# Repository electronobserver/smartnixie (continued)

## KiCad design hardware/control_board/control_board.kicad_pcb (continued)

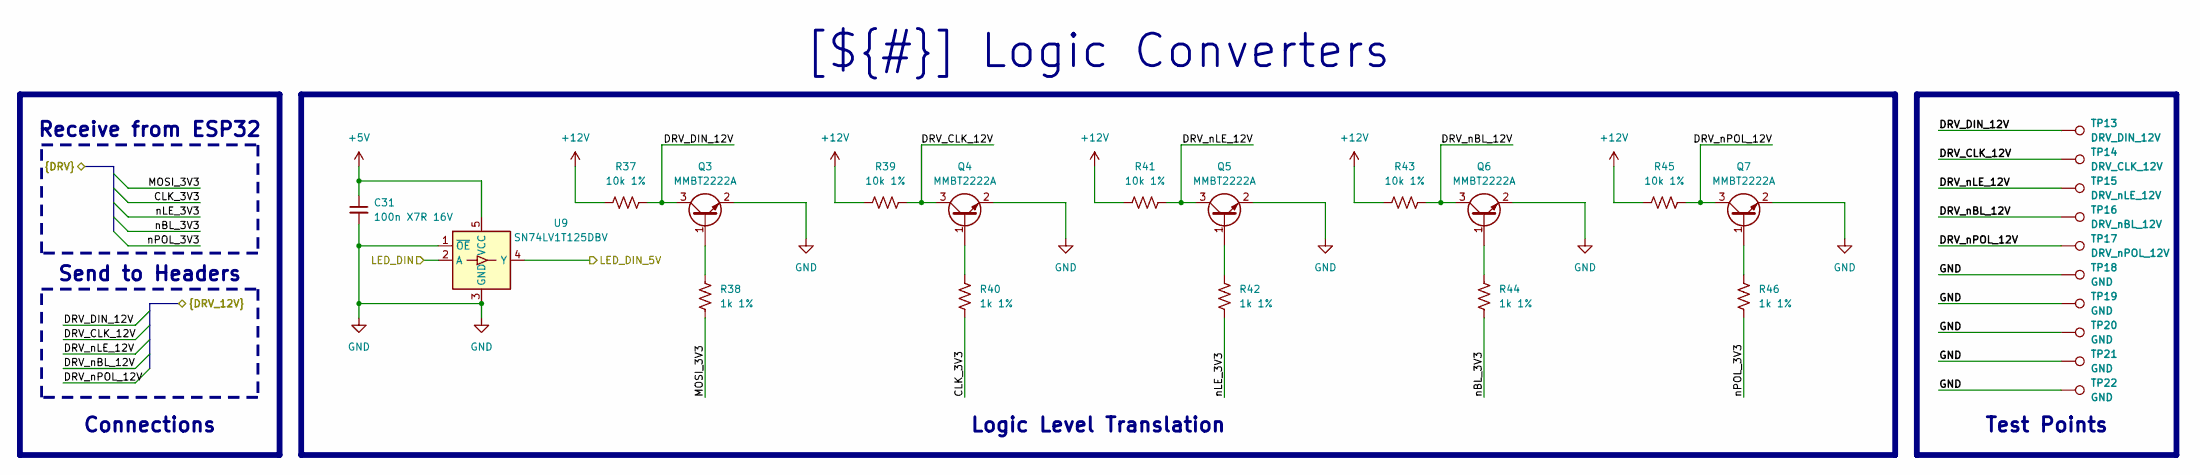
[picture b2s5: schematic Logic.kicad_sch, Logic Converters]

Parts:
C31: 100n X7R 16V; C_0805_2012Metric_Pad1.18x1.45mm_HandSolder; Part No. CC0805KRX7R7BB104
Q3, Q4, Q5, Q6, Q7: MMBT2222A; SOT-23
R37, R39, R41, R43, R45: 10k 1%; R_0402_1005Metric_Pad0.72x0.64mm_HandSolder; Part No. AC0402FR-07107KL
R38, R40, R42, R44, R46: 1k 1%; R_0402_1005Metric_Pad0.72x0.64mm_HandSolder; Part No. ERJ-2RKF1001X
TP13: DRV_DIN_12V; TestPoint_Pad_D1.0mm
TP14: DRV_CLK_12V; TestPoint_Pad_D1.0mm
TP15: DRV_nLE_12V; TestPoint_Pad_D1.0mm
TP16: DRV_nBL_12V; TestPoint_Pad_D1.0mm
TP17: DRV_nPOL_12V; TestPoint_Pad_D1.0mm
TP18, TP19, TP20, TP21, TP22: GND; TestPoint_Pad_D1.0mm
U9: SN74LV1T125DBV; SOT-23-5

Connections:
+5V: C31.1, U9.5 (VCC); also elsewhere on the board
+12V: R37.1, R39.1, R41.1, R43.1, R45.1; also elsewhere on the board
/Block Diagram/Logic Conversion/CLK_3V3: R40.1; also elsewhere on the board
/Block Diagram/Logic Conversion/DRV_CLK_12V: Q4.3 (C), R39.2, TP14.1; also elsewhere on the board
/Block Diagram/Logic Conversion/DRV_DIN_12V: Q3.3 (C), R37.2, TP13.1; also elsewhere on the board
/Block Diagram/Logic Conversion/DRV_nBL_12V: Q6.3 (C), R43.2, TP16.1; also elsewhere on the board
/Block Diagram/Logic Conversion/DRV_nLE_12V: Q5.3 (C), R41.2, TP15.1; also elsewhere on the board
/Block Diagram/Logic Conversion/DRV_nPOL_12V: Q7.3 (C), R45.2, TP17.1; also elsewhere on the board
/Block Diagram/Logic Conversion/LED_DIN_5V: U9.4 (Y); also elsewhere on the board
/Block Diagram/Logic Conversion/MOSI_3V3: R38.1; also elsewhere on the board
/Block Diagram/Logic Conversion/nBL_3V3: R44.1; also elsewhere on the board
/Block Diagram/Logic Conversion/nLE_3V3: R42.1; also elsewhere on the board
/Block Diagram/Logic Conversion/nPOL_3V3: R46.1; also elsewhere on the board
/Block Diagram/MCU/LED_DIN: U9.2 (A); also elsewhere on the board
GND: C31.2, Q3.2 (E), Q4.2 (E), Q5.2 (E), Q6.2 (E), Q7.2 (E), TP18.1, TP19.1, TP20.1, TP21.1, TP22.1, U9.1 (~OE), U9.3 (GND); also elsewhere on the board
unnamed: Q3.1 (B), R38.2
unnamed: Q4.1 (B), R40.2
unnamed: Q5.1 (B), R42.2
unnamed: Q6.1 (B), R44.2
unnamed: Q7.1 (B), R46.2

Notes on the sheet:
[${#}] ${TITLE}
Test Points
Connections
Logic Level Translation
Send to Headers
Receive from ESP32

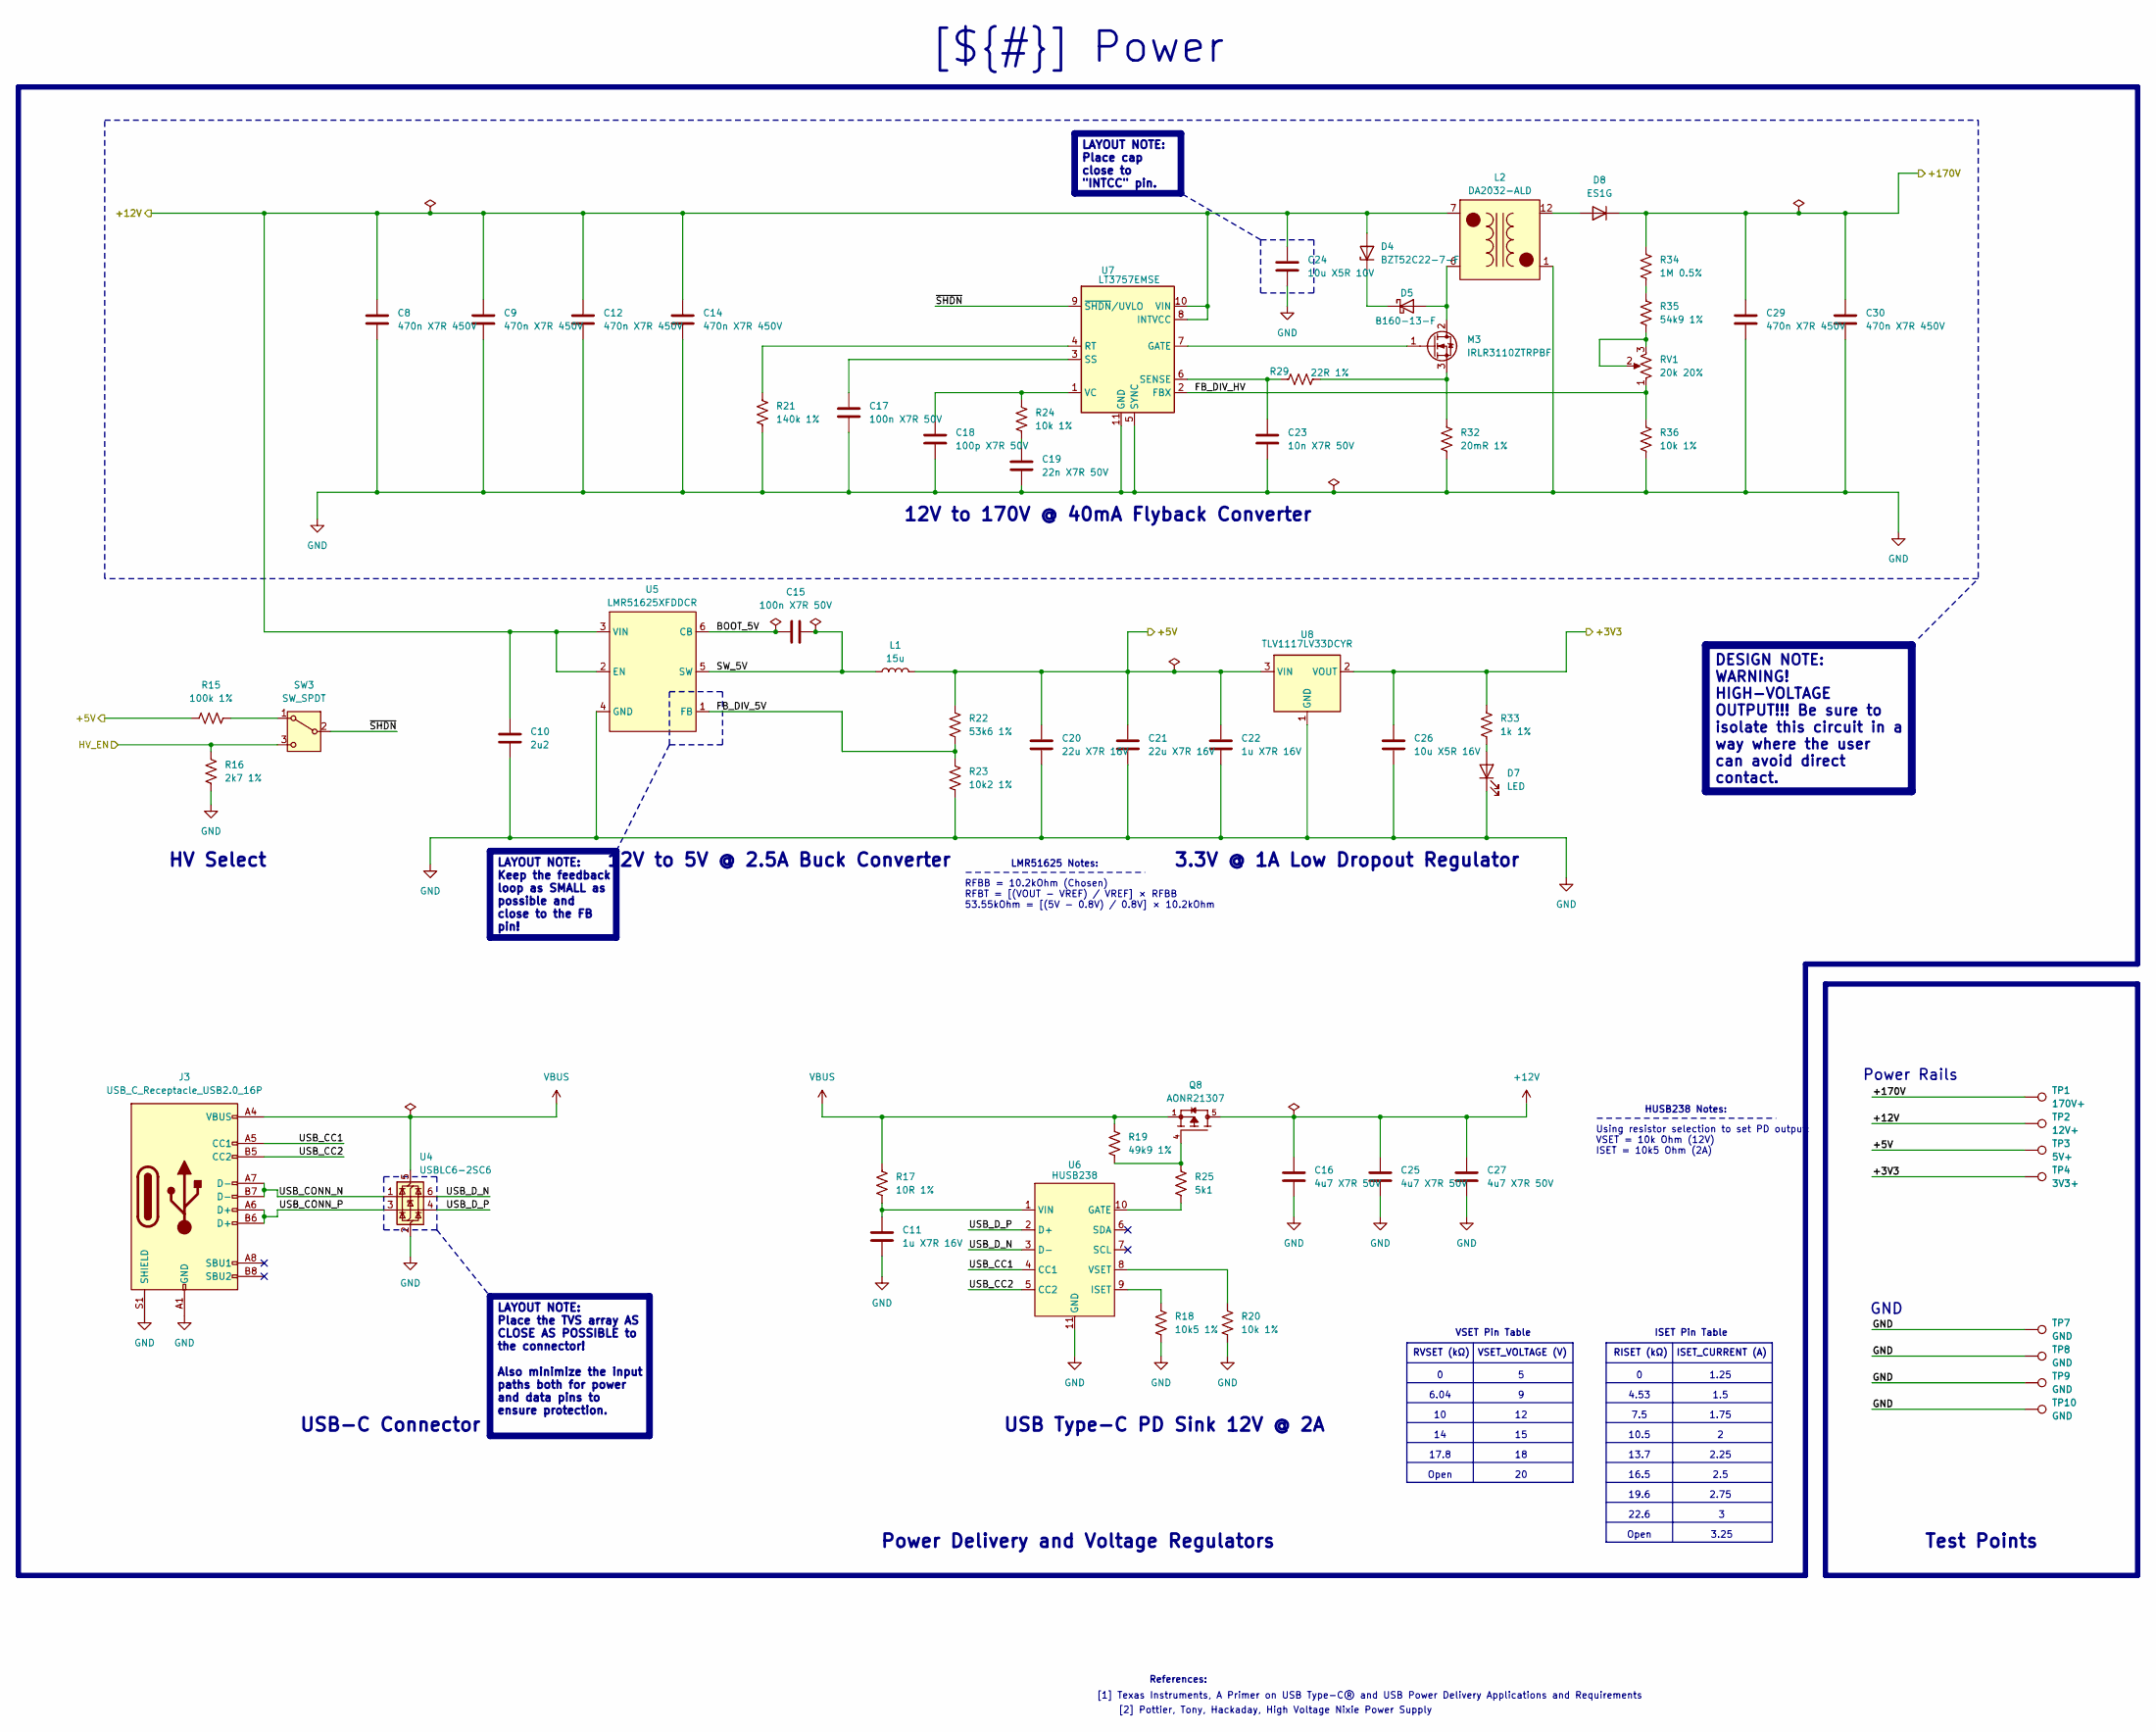
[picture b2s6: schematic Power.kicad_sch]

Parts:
C8, C9, C12, C14, C29, C30: 470n X7R 450V; C_1206_3216Metric_Pad1.33x1.80mm_HandSolder; Part No. LMK316BJ476ML-T
C10: 2u2; C_1206_3216Metric_Pad1.33x1.80mm_HandSolder; Part No. GCJ31CR71H225KA12L
C11, C22: 1u X7R 16V; C_0805_2012Metric_Pad1.18x1.45mm_HandSolder; Part No. GRM21BR71C105KA01L
C15, C17: 100n X7R 50V; C_0603_1608Metric_Pad1.08x0.95mm_HandSolder; Part No. CC0603KRX7R9BB104
C16, C25, C27: 4u7 X7R 50V; C_1206_3216Metric_Pad1.33x1.80mm_HandSolder; Part No. GRM31CR71H475KA12L
C18: 100p X7R 50V; C_0603_1608Metric_Pad1.08x0.95mm_HandSolder; Part No. CC0603KRX7R9BB101
C19: 22n X7R 50V; C_0603_1608Metric_Pad1.08x0.95mm_HandSolder; Part No. CC0603KRX7R9BB223
C20, C21: 22u X7R 16V; C_1206_3216Metric_Pad1.33x1.80mm_HandSolder; Part No. GRM31CR61C476ME44
C23: 10n X7R 50V; C_0603_1608Metric_Pad1.08x0.95mm_HandSolder; Part No. CC0603KRX7R9BB103
C24: 10u X5R 10V; C_0603_1608Metric_Pad1.08x0.95mm_HandSolder; Part No. CL10A106MP8NNNC
C26: 10u X5R 16V; C_0805_2012Metric_Pad1.18x1.45mm_HandSolder; Part No. GRM21BR61C106KE15K
D4: BZT52C22-7-F; D_SOD-123
D5: B160-13-F; D_SMA_Handsoldering
D7: LED; LED_0402_1005Metric_Pad0.77x0.64mm_HandSolder; Part No. VLMG1500-GS08
D8: ES1G; D_SMA_Handsoldering
J3: USB_C_Receptacle_USB2.0_16P; USB_C_Receptacle_HRO_TYPE-C-31-M-12; Part No. 10155435-00011LF
L1: 15u; L_Abracon_ASPI-0630LR-150M-T15
L2: DA2032-ALD; DA2032-AL
M3: IRLR3110ZTRPBF; TO-252-2
Q8: AONR21307; TRANS_AONR21307; PARTREV 1.1
R15: 100k 1%; R_0402_1005Metric_Pad0.72x0.64mm_HandSolder; Part No. ERJ-2RKF1003X
R16: 2k7 1%; R_0402_1005Metric_Pad0.72x0.64mm_HandSolder; Part No. ERJ-2GEJ272X
R17: 10R 1%; R_0603_1608Metric_Pad0.98x0.95mm_HandSolder; Part No. RMCF0603FT10R0
R18: 10k5 1%; R_0603_1608Metric_Pad0.98x0.95mm_HandSolder; Part No. Stackpole Electronics Inc
R19: 49k9 1%; R_0603_1608Metric_Pad0.98x0.95mm_HandSolder; Part No. RMCF0603FT49K9
R20, R24, R36: 10k 1%; R_0603_1608Metric_Pad0.98x0.95mm_HandSolder; Part No. RC0603FR-0710KL
R21: 140k 1%; R_0603_1608Metric_Pad0.98x0.95mm_HandSolder; Part No. RC0603FR-07140KL
R22: 53k6 1%; R_0201_0603Metric_Pad0.64x0.40mm_HandSolder; Part No. RC0603FR-0753K6L
R23: 10k2 1%; R_0201_0603Metric_Pad0.64x0.40mm_HandSolder; Part No. RMCF0603FT10K2
R25: 5k1; R_0603_1608Metric_Pad0.98x0.95mm_HandSolder; Part No. RC0603FR-075K1L
R29: 22R 1%; R_0603_1608Metric_Pad0.98x0.95mm_HandSolder; Part No. RC0603FR-0722RL
R32: 20mR 1%; R_1206_3216Metric_Pad1.30x1.75mm_HandSolder; Part No. PE1206FRF470R02L
R33: 1k 1%; R_0402_1005Metric_Pad0.72x0.64mm_HandSolder; Part No. ERJ-2RKF1001X
R34: 1M 0.5%; R_1206_3216Metric_Pad1.30x1.75mm_HandSolder; Part No. RT1206DRE071ML
R35: 54k9 1%; R_0201_0603Metric_Pad0.64x0.40mm_HandSolder; Part No. RC0603FR-0754K9L
RV1: 20k 20%; Potentiometer-3313J; Part No. 3313J-1-203E
SW3: SW_SPDT; CLSB12B01T; Part No. CL-SB-12B-01T
TP1: 170V+; TestPoint_Pad_D1.0mm
TP2: 12V+; TestPoint_Pad_D1.0mm
TP3: 5V+; TestPoint_Pad_D1.0mm
TP4: 3V3+; TestPoint_Pad_D1.0mm
TP7, TP8, TP9, TP10: GND; TestPoint_Pad_D1.0mm
U4: USBLC6-2SC6; SOT-23-6
U5: LMR51625XFDDCR; TSOT-23-6
U6: HUSB238; DFN-10_3x3mm
U7: LT3757EMSE; MSOP-10-1EP_3x3mm_P0.5mm_EP1.68x1.88mm_ThermalVias
U8: TLV1117LV33DCYR; SOT-223

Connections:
+3V3: C26.1, R33.2, TP4.1, U8.2 (VOUT), U8.4; also elsewhere on the board
+5V: C20.1, C21.1, C22.1, L1.2, R15.1, R22.1, TP3.1, U8.3 (VIN); also elsewhere on the board
+12V: C8.1, C9.1, C10.1, C12.1, C14.1, C16.1, C24.1, C25.1, C27.1, D4.2 (A), L2.7, L2.8, L2.9, L2.10, Q8.5, Q8.6, Q8.7, Q8.8, TP2.1, U5.2 (EN), U5.3 (VIN), U7.8 (INTVCC), U7.10 (VIN); also elsewhere on the board
+170V: C29.1, C30.1, D8.1 (K), R34.1, TP1.1; also elsewhere on the board
/Block Diagram/MCU/HV_EN: R16.1, SW3.3 (C); also elsewhere on the board
/Block Diagram/Power/BOOT_5V: C15.1, U5.6 (CB)
/Block Diagram/Power/FB_DIV_5V: R22.2, R23.1, U5.1 (FB)
/Block Diagram/Power/FB_DIV_HV: R36.1, RV1.1, U7.2 (FBX)
/Block Diagram/Power/SW_5V: C15.2, L1.1, U5.5 (SW)
/Block Diagram/Power/USB_CC1: J3.A5 (CC1), U6.4 (CC1)
/Block Diagram/Power/USB_CC2: J3.B5 (CC2), U6.5 (CC2)
/Block Diagram/Power/USB_CONN_N: J3.A7 (D-), J3.B7 (D-), U4.1 (I/O1)
/Block Diagram/Power/USB_CONN_P: J3.A6 (D+), J3.B6 (D+), U4.3 (I/O2)
/Block Diagram/Power/USB_D_N: U4.6 (I/O1), U6.3 (D-)
/Block Diagram/Power/USB_D_P: U4.4 (I/O2), U6.2 (D+)
/Block Diagram/Power/~SHDN: SW3.2 (B), U7.9 (~SHDN/UVLO)
GND: C8.2, C9.2, C10.2, C11.2, C12.2, C14.2, C16.2, C17.2, C18.2, C19.2, C20.2, C21.2, C22.2, C23.2, C24.2, C25.2, C26.2, C27.2, C29.2, C30.2, D7.1 (K), J3.A1 (GND), J3.A12 (GND), J3.B1 (GND), J3.B12 (GND), J3.S1 (SHIELD), L2.1, R16.2, R18.2, R20.2, R21.2, R23.2, R32.2, R36.2, TP7.1, TP8.1, TP9.1, TP10.1, U4.2 (GND), U5.4 (GND), U6.11 (GND), U7.5 (SYNC), U7.11 (GND), U8.1 (GND); also elsewhere on the board
unnamed: C19.1, R24.2
unnamed: D4.1 (K), D5.1 (K)
unnamed: D5.2 (A), L2.3, L2.4, L2.5, L2.6, M3.2
unnamed: D7.2 (A), R33.1
unnamed: D8.2 (A), L2.12
unnamed: M3.3, R29.2, R32.1
unnamed: Q8.4, R19.2, R25.1
unnamed: R34.2, R35.1
unnamed: R35.2, RV1.2, RV1.3
unnamed: R15.2, SW3.1 (A)
unnamed: R25.2, U6.10 (GATE)
unnamed: R18.1, U6.9 (ISET)
unnamed: C11.1, R17.2, U6.1 (VIN)
unnamed: R20.1, U6.8 (VSET)
unnamed: M3.1, U7.7 (GATE)
unnamed: R21.1, U7.4 (RT)
unnamed: C23.1, R29.1, U7.6 (SENSE)
unnamed: C17.1, U7.3 (SS)
unnamed: C18.1, R24.1, U7.1 (VC)
VBUS: J3.A4 (VBUS), J3.A9 (VBUS), J3.B4 (VBUS), J3.B9 (VBUS), Q8.1, Q8.2, Q8.3, R17.1, R19.1, U4.5 (VBUS)

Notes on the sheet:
LAYOUT NOTE: Keep the feedback loop as SMALL as possible and close to the FB pin!
LAYOUT NOTE: Place the TVS array AS CLOSE AS POSSIBLE to the connector! Also minimize the input paths both for power and data pins to ensure protection.
DESIGN NOTE: WARNING! HIGH-VOLTAGE OUTPUT!!! Be sure to isolate this circuit in a way where the user can avoid direct contact.
USB Type-C PD Sink 12V @ 2A
USB-C Connector
HV Select
[${#}] ${TITLE}
Power Delivery and Voltage Regulators
12V to 170V @ 40mA Flyback Converter
12V to 5V @ 2.5A Buck Converter
Test Points
3.3V @ 1A Low Dropout Regulator
LAYOUT NOTE: Place cap close to "INTCC" pin.
GND
RFBB = 10.2kOhm (Chosen) RFBT = [(VOUT − VREF) / VREF] × RFBB 53.55kOhm = [(5V − 0.8V) / 0.8V] × 10.2kOhm
2.25
[2] Pottier, Tony, Hackaday, High Voltage Nixie Power Supply
13.7
[1] Texas Instruments, A Primer on USB Type-C® and USB Power Delivery Applications and Requirements
LMR51625 Notes:
7.5
4.53
10.5
19.6
Open
2.5
3.25
ISET Pin Table
Using resistor selection to set PD output: VSET = 10k Ohm (12V) ISET = 10k5 Ohm (2A)
16.5
References:
2.75
ISET_CURRENT (A)
VSET_VOLTAGE (V)
6.04
RISET (kΩ)
22.6
VSET Pin Table
1.5
1.25

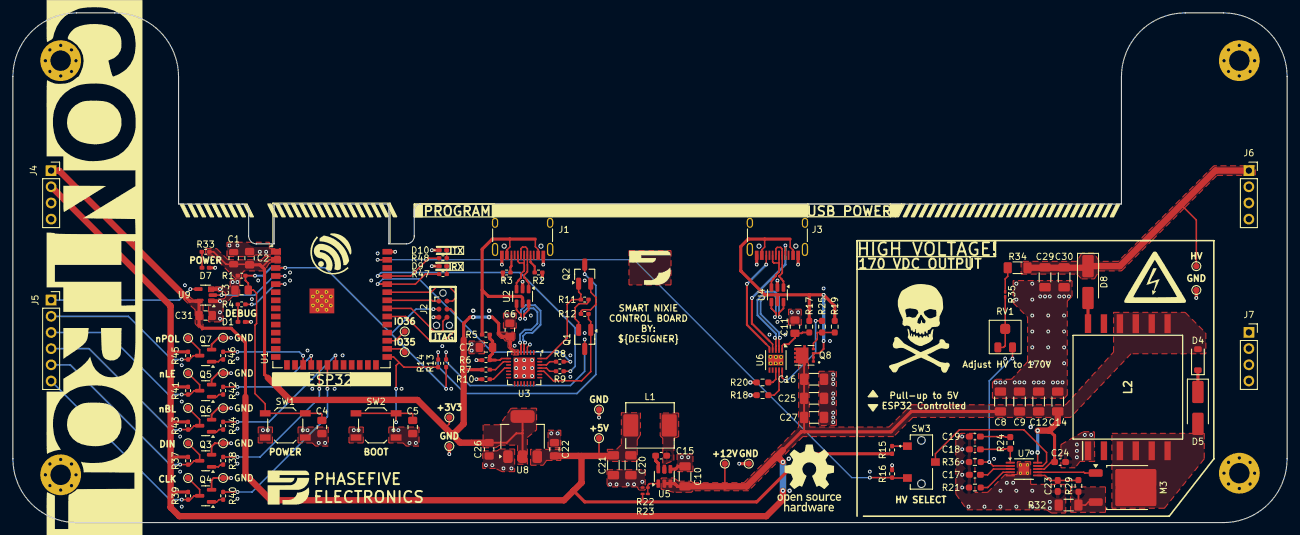
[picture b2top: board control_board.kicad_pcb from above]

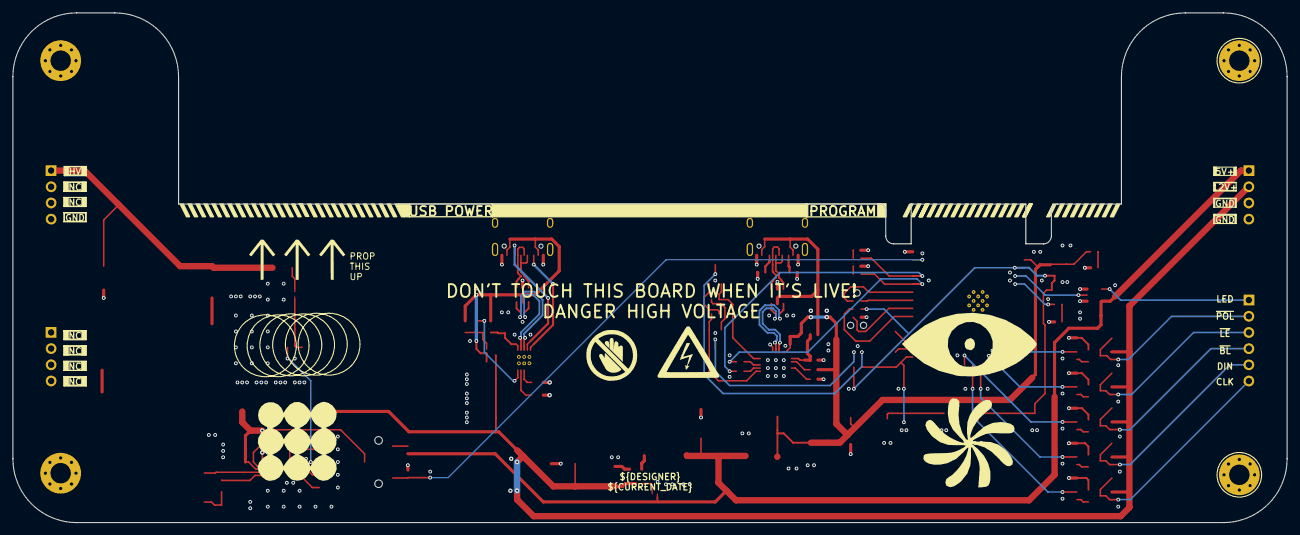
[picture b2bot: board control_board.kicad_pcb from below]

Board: 4 copper layers, 200.0 x 80.0 mm, 149 parts (8 on the bottom side), 86 nets.

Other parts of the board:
G1, G8: LOGO; P5Logo
G2: LOGO; AbstractDecal1
G3: LOGO; OSHW
G3#2: LOGO; SidePanelArt
G4: LOGO; Expressif
G5: LOGO; NoTouch
G6, G11: LOGO; HV
G7: LOGO; AbstractDecal3
G9: LOGO; AbstractDecal2
G10: LOGO; Skull
G12, G13, G14: LOGO; Arrow

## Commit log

2025-11-08 Adding Worksheet templates
2025-11-08 Tweaking existing gerber files and schematics to comply with new project structure
2025-11-08 Removing images generated for silkscreen art and only keeping ones used directly in schematic
2025-11-08 Minor improvements + redirecting footprints to map to the general 3D models folder
